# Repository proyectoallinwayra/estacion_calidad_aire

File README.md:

# Estacion de Monitoreo de la Calidad Aire

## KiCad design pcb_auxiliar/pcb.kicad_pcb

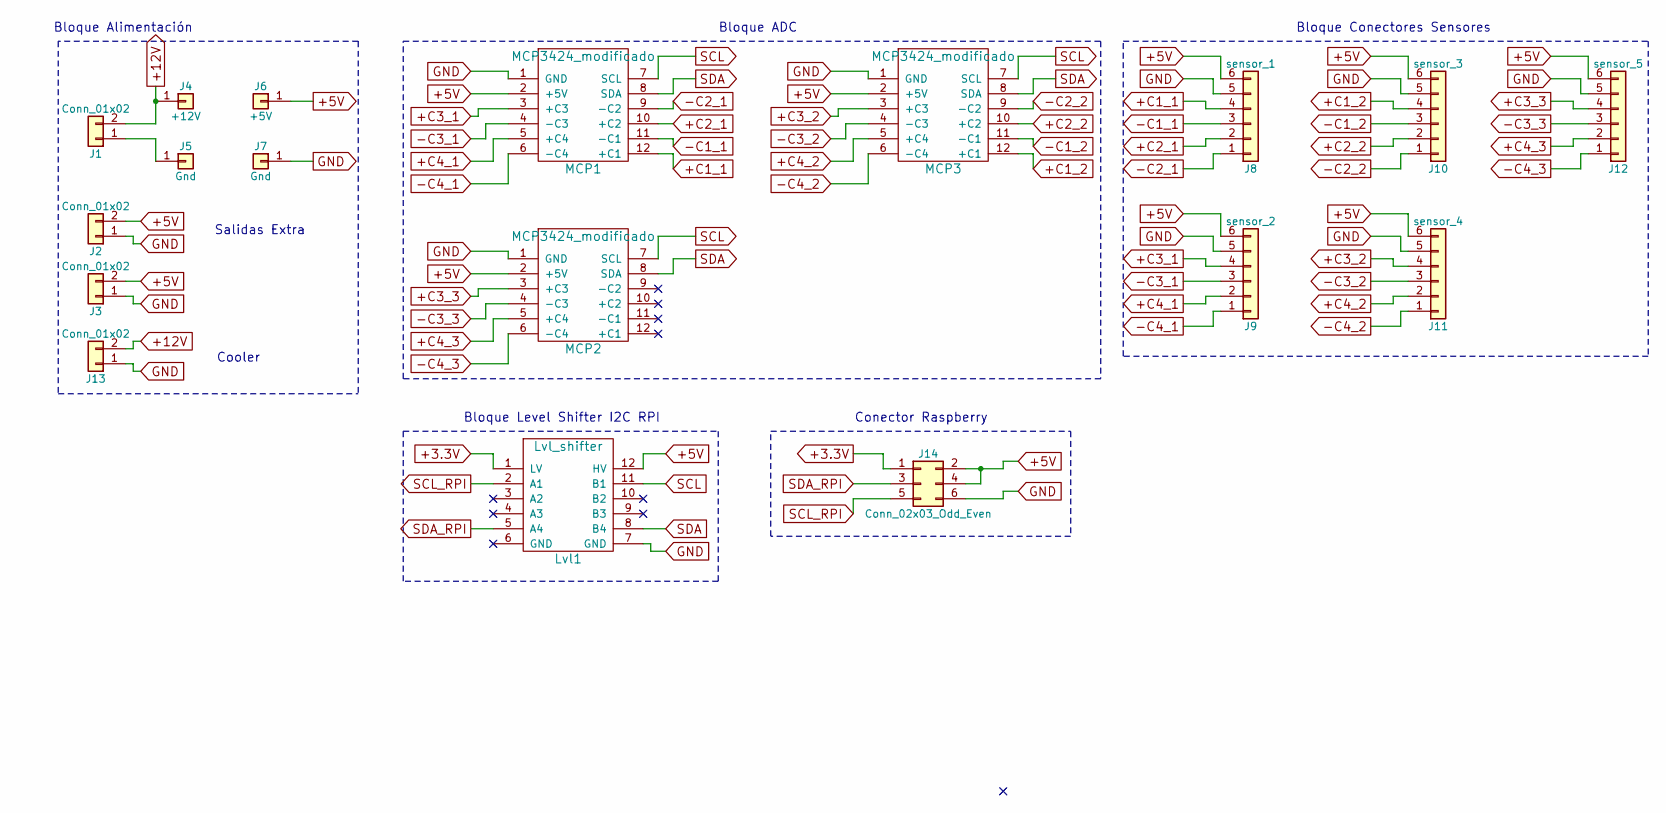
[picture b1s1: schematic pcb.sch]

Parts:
J1: Conn_01x02; bornier2
J2, J3, J13: Conn_01x02; Pin_Header_Straight_1x02_Pitch2.54mm
J4: +12V; Pin_Header_Straight_1x01_Pitch2.54mm
J5, J7: Gnd; Pin_Header_Straight_1x01_Pitch2.54mm
J6: +5V; Pin_Header_Straight_1x01_Pitch2.54mm
J8: sensor_1; Molex_KK-6410-06_06x2.54mm_Straight
J9: sensor_2; Molex_KK-6410-06_06x2.54mm_Straight
J10: sensor_3; Molex_KK-6410-06_06x2.54mm_Straight
J11: sensor_4; Molex_KK-6410-06_06x2.54mm_Straight
J12: sensor_5; Molex_KK-6410-06_06x2.54mm_Straight
J14: Conn_02x03_Odd_Even; Pin_Header_Straight_2x03_Pitch2.54mm
Lvl1: Lvl_shifter; LOGIC_LEVEL_CONVERTER
MCP1, MCP2, MCP3: MCP3424_modificado; mcp3424

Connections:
+3.3V: J14.1, Lvl1.1 (LV)
+5V: J2.2, J3.2, J6.1, J8.6, J9.6, J10.6, J11.6, J12.6, J14.2, J14.4, Lvl1.12 (HV), MCP1.2 (+5V), MCP2.2 (+5V), MCP3.2 (+5V)
+12V: J1.2, J4.1, J13.2
+C1_1: J8.4, MCP1.12 (+C1)
+C1_2: J10.4, MCP3.12 (+C1)
+C2_1: J8.2, MCP1.10 (+C2)
+C2_2: J10.2, MCP3.10 (+C2)
+C3_1: J9.4, MCP1.3 (+C3)
+C3_2: J11.4, MCP3.3 (+C3)
+C3_3: J12.4, MCP2.3 (+C3)
+C4_1: J9.2, MCP1.5 (+C4)
+C4_2: J11.2, MCP3.5 (+C4)
+C4_3: J12.2, MCP2.5 (+C4)
-C1_1: J8.3, MCP1.11 (-C1)
-C1_2: J10.3, MCP3.11 (-C1)
-C2_1: J8.1, MCP1.9 (-C2)
-C2_2: J10.1, MCP3.9 (-C2)
-C3_1: J9.3, MCP1.4 (-C3)
-C3_2: J11.3, MCP3.4 (-C3)
-C3_3: J12.3, MCP2.4 (-C3)
-C4_1: J9.1, MCP1.6 (-C4)
-C4_2: J11.1, MCP3.6 (-C4)
-C4_3: J12.1, MCP2.6 (-C4)
GND: J2.1, J3.1, J7.1, J8.5, J9.5, J10.5, J11.5, J12.5, J13.1, J14.6, Lvl1.7 (GND), MCP1.1 (GND), MCP2.1 (GND), MCP3.1 (GND)
unnamed: J1.1, J5.1
SCL: Lvl1.11 (B1), MCP1.7 (SCL), MCP2.7 (SCL), MCP3.7 (SCL)
SCL_RPI: J14.5, Lvl1.2 (A1)
SDA: Lvl1.8 (B4), MCP1.8 (SDA), MCP2.8 (SDA), MCP3.8 (SDA)
SDA_RPI: J14.3, Lvl1.5 (A4)

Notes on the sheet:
Bloque ADC
Bloque Conectores Sensores
Bloque Level Shifter I2C RPI
Bloque Alimentación
Conector Raspberry
Cooler
Salidas Extra

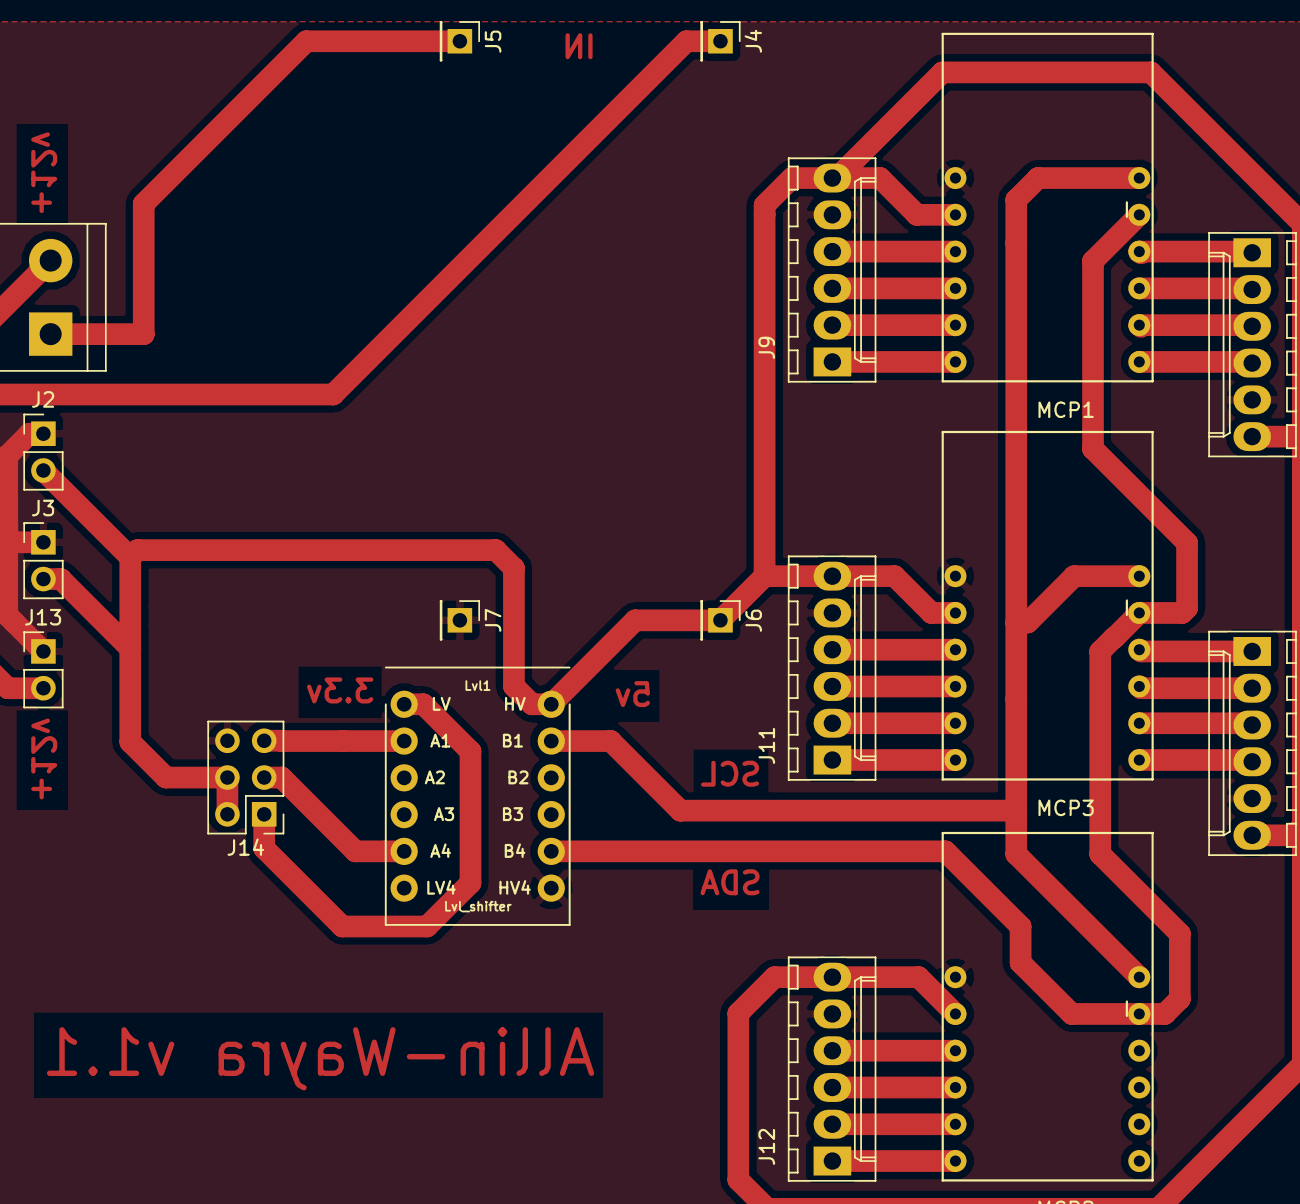
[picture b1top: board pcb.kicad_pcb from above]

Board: 2 copper layers, 18 parts (0 on the bottom side), 29 nets.

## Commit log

2018-08-30 Comentario
2018-08-30 Se agrego carpeta con archivos de corte laser
2018-08-31 Se agrega la carpeta con el diseño del pcb.
2018-08-31 Prueba
2018-08-31 se borro archivo
2018-08-31 Se agregaron carpetas pagina web y estructura 3d
    se agregaron carpetas pagina web y estructura 3d
2018-09-01 Se eliminaron archivos que no eran utiles
2018-09-01 Se borraron archivos innecesarios
